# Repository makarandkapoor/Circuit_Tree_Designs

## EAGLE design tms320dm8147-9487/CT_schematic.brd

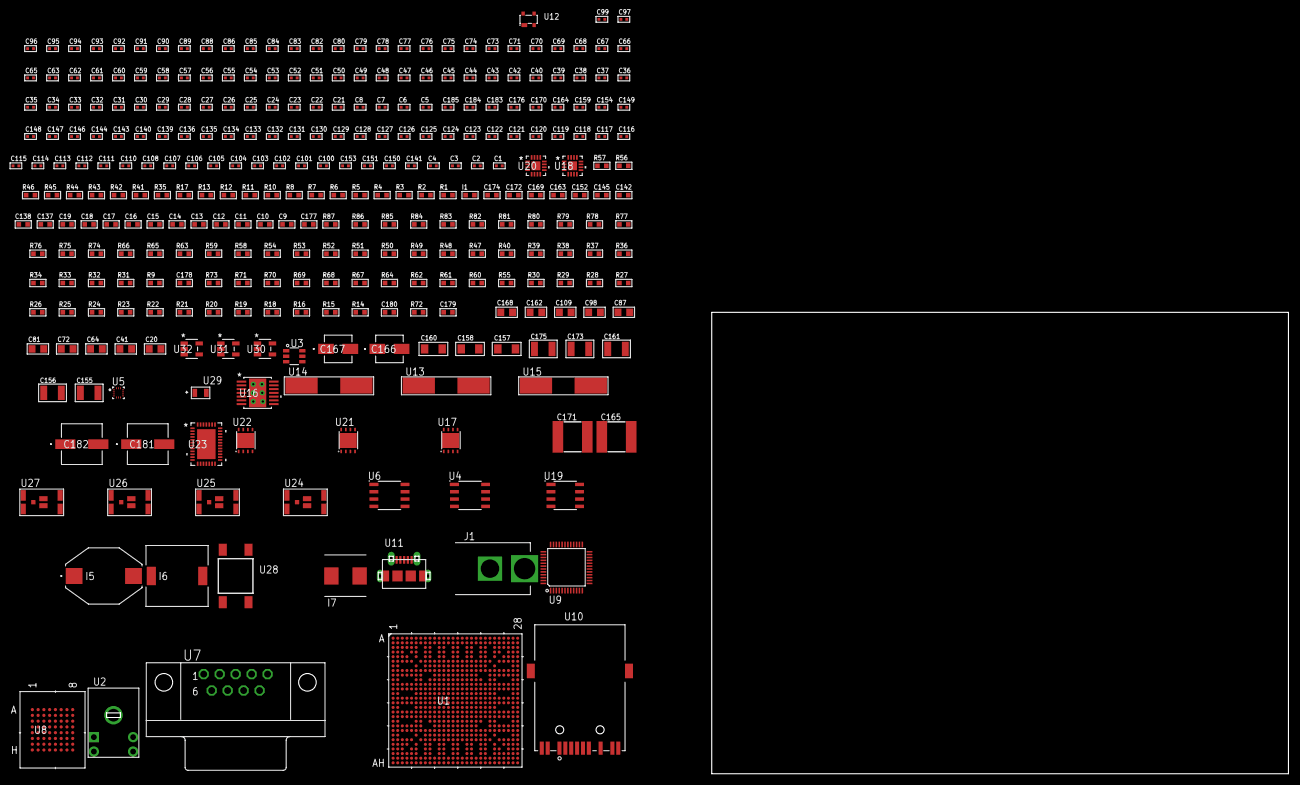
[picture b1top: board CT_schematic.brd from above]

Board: 2 copper layers, 309 parts (0 on the bottom side), 194 nets, no tracks yet.

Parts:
C1, C2, C3, C4: 1.2e-11; C0402
C5, C6, C7, C8, C21, C22, C23, C24, C25, C26, C27, C28, C29, C30, C42, C43, C44, C45, C46, C47, C48, C49, C50, C51, C52, C53, C54, C55, C56, C57, C58, C59, C60, C61, C62, C63, C65, C66, C67, C68, C69, C70, C71, C73, C74, C75, C76, C77, C78, C79, C80, C82, C83, C84, C85, C86, C135, C136, C143, C146, C148, C149, C154, C164, C170, C176: 1e-07; C0402
C9, C10, C11, C12, C13, C14, C15, C16, C17, C18, C19, C137, C138, C142, C145, C152, C163, C169, C172, C174: 1e-06; C0603
C20, C41, C64, C72, C81, C87, C98, C109, C162, C168: 1e-05; C0805
C31, C32, C33, C34, C35, C36, C37, C38, C39, C40, C88, C89, C90, C91, C92, C93, C94, C95, C96, C97, C99, C100, C101, C102, C103, C104, C105, C106, C107, C108, C110, C111, C112, C113, C114, C115, C116, C117, C118, C119, C120, C121, C122, C123, C124, C125, C126, C127, C128, C129, C130, C131, C132, C133, C134, C139, C140, C144, C147, C159, C183, C184, C185: 1e-08; C0402
C141: 2.2e-08; C0402
C150, C151: 2.7e-11; C0402
C153: 3.3e-09; C0402
C155, C156: 2.2e-05; C1210
C157, C158, C160: 1e-05; C1206
C161, C173, C175: 1e-05; C1210
C165, C171: 6.8e-05; 2220
C166: 1e-06; EXV-9B
C167: 2.2e-06; EXV-9B
C177: 2.2e-06; C0603
C178: 2.45e-08; R0603
C179: 2.8258362168397e-09; R0603
C180: 7.105e-09; R0603
C181, C182: 0.0001; EXV-9H
I1: 97.0; R0603
I5: 1.5e-06; IND_PM3316
I6: 2.5e-06; DR1040
I7: 3.3e-06; WE-HCI_7030/7040/7050
J1: PJ-037B; PJ-037B_PACKAGE
R1, R2, R3, R4, R46: 4700.0; R0603
R5, R6, R7, R8: 2200.0; R0603
R9, R63: 47000.0; R0603
R10, R11: 49.9; R0603
R12, R13: 2700.0; R0603
R14, R15, R16, R18, R19, R20, R21, R22, R23, R24, R25, R26, R27, R28, R29, R30, R55, R61, R62, R64, R68, R70, R71, R73: 100000.0; R0603
R17, R41, R42: 0.1; R0603
R31, R32, R33, R34, R36, R37, R38, R39, R40, R47, R48, R49, R50, R51, R52, R74, R76, R77, R82, R83, R84, R85, R86: 10000.0; R0603
R35: 120.0; R0603
R43, R44: 200.0; R0603
R45: 2490.0; R0603
R53: 15000.0; R0603
R54: 22000.0; R0603
R56: 3900.0; R0603
R57: 1000.0; R0603
R58, R65: 20000.0; R0603
R59: 27000.0; R0603
R60, R67, R69: 300000.0; R0603
R66: 91000.0; R0603
R72: 153694.38; R0603
R75, R87: 75000.0; R0603
R78, R79, R80, R81: 95300.0; R0603
U1: TMS320DM8147SCYE2; BFBGA-684
U2: MD-40S
U3: MAX4995AAUT+T; SOT-23-6
U4: AT25M01-SSHM-T; SOIC-8
U5: BMC150; LGA14R35P5X6_200X200X100
U6: MCP2562-E/SN; SOIC-8
U7: 182-009-113R531; 182-009-MALE
U8: MT28EW128ABA1HPC-0SIT; LBGA-64
U9: RTL8201FL-VB-CG
U10: 7498011122R
U11: 47590-0001; MICRO_USB_AB
U12: prtr5v0u2ax; SOT143B
U13, U14: ABLS-20.000MHZ-B4-T
U15: ABLS-25.000MHZ-B2F-T
U16: tps54525PWP; HTSSOP14
U17: LP3878SDX-ADJ/NOPB; WSON-8
U18, U20: LTC3601EUD#PBF; QFN-16_EP
U19: LP2954AIMX/NOPB; LP2954
U21, U22: LP2951ACSDX/NOPB; WSON-8
U23: LTC2928CUHF#PBF; QFN-38_UHF
U24, U25, U26, U27: IRF8306MTRPbF; IRF8306MTRPBF
U28: 4-1437565-2; SW_4-1437565-2
U29: Q65110A2395; LGM67K-G1J2-24-Z
U30, U31, U32: nc7sz125m5x; NC7SZ125M5X

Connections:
CLK_CRYSTAL_U1_AH2: C1.1, U1.AH2, U13.1
CLK_CRYSTAL_U1_AH3: C2.1, U1.AH3, U13.2
CLK_CRYSTAL_U1_R1: C3.1, U1.R1, U14.1
CLK_CRYSTAL_U1_T1: C4.1, U1.T1, U14.2
CLK_CRYSTAL_U9_42: C151.1, U9.42, U15.1
CLK_CRYSTAL_U9_43: C150.1, U9.43, U15.2
GND: C1.2, C2.2, C3.2, C4.2, C5.2, C6.2, C7.2, C8.2, C9.2, C10.2, C11.2, C12.2, C13.2, C14.2, C15.2, C16.2, C17.2, C18.2, C19.2, C20.2, C21.2, C22.2, C23.2, C24.2, C25.2, C26.2, C27.2, C28.2, C29.2, C30.2, C31.2, C32.2, C33.2, C34.2, C35.2, C36.2, C37.2, C38.2, C39.2, C40.2, C41.2, C42.2, C43.2, C44.2, C45.2, C46.2, C47.2, C48.2, C49.2, C50.2, C51.2, C52.2, C53.2, C54.2, C55.2, C56.2, C57.2, C58.2, C59.2, C60.2, C61.2, C62.2, C63.2, C64.2, C65.2, C66.2, C67.2, C68.2, C69.2, C70.2, C71.2, C72.2, C73.2, C74.2, C75.2, C76.2, C77.2, C78.2, C79.2, C80.2, C81.2, C82.2, C83.2, C84.2, C85.2, C86.2, C87.2, C88.2, C89.2, C90.2, C91.2, C92.2, C93.2, C94.2, C95.2, C96.2, C97.2, C98.2, C99.2, C100.2, C101.2, C102.2, C103.2, C104.2, C105.2, C106.2, C107.2, C108.2, C109.2, C110.2, C111.2, C112.2, C113.2, C114.2, C115.2, C116.2, C117.2, C118.2, C119.2, C120.2, C121.2, C122.2, C123.2, C124.2, C125.2, C126.2, C127.2, C128.2, C129.2, C130.2, C131.2, C132.2, C133.2, C134.2, C135.2, C136.2, C137.2, C138.2, C139.2, C140.2, C141.2, C142.2, C143.2, C144.2, C145.2, C146.2, C147.2, C148.2, C149.2, C150.2, C151.2, C152.2, C153.2, C155.2, C156.2, C157.2, C158.2, C159.2, C160.2, C161.2, C162.2, C163.2, C165.1, C165.2, C166.2, C167.2, C168.2, C169.2, C171.1, C171.2, C172.2, C173.2, C174.2, C175.2, C176.2, C177.2, C178.2, C179.2, C180.2, C181.2, C182.2, C183.2, C184.2, C185.2, J1.2, R9.2, R10.2, R11.2, R14.2, R15.2, R16.2, R17.2, R18.2, R19.2, R20.2, R21.2, R22.2, R23.2, R24.2, R25.2, R26.2, R27.2, R28.2, R29.2, R30.2, R41.2, R42.2, R45.2, R47.2, R49.2, R50.2, R54.2, R57.2, R58.2, R60.2, R64.2, R65.2, R67.2, R70.2, R73.2, R75.2, R78.2, R79.2, R80.2, R81.2, R82.2, R83.2, R84.2, R85.2, R86.2, U1.A1, U1.A12, U1.A17, U1.A28, U1.AA14, U1.AA16, U1.AA19, U1.AD21, U1.AE1, U1.AE2, U1.AE9, U1.AE20, U1.AF23, U1.AG1, U1.AG3, U1.AH1, U1.AH28, U1.D9, U1.D20, U1.E8, U1.E20, U1.J12, U1.J14, U1.J19, U1.K10, U1.K11, U1.K13, U1.K14, U1.K15, U1.K16, U1.K17, U1.K19, U1.L8, U1.L13, U1.L14, U1.L16, U1.L22, U1.M9, U1.M15, U1.M17, U1.M19, U1.M21, U1.N8, U1.N12, U1.N15, U1.N16, U1.N20, U1.N21, U1.N22, U1.P13, U1.P15, U1.P17, U1.P19, U1.P21, U1.R2, U1.R8, U1.R9, U1.R10, U1.R12, U1.R14, U1.R16, U1.R21, U1.R22, U1.T8, U1.T9, U1.T13, U1.T14, U1.T17, U1.T18, U1.T19, U1.T21, U1.T22, U1.U12, U1.U14, U1.U18, U1.U20, U1.U26, U1.V7, U1.V9, U1.V11, U1.V12, U1.V13, U1.V17, U1.V18, U1.V19, U1.V21, U1.W12, U1.W16, U1.W17, U1.Y1, U1.Y2, U1.Y10, U1.Y12, U1.Y15, U1.Y17, U1.Y18, U1.Y19, U1.Y26, U2.1, U2.2, U3.2, U4.4, U5.1, U5.6, U5.7, U5.9, U6.2, U6.8, U7.5, U8.E8, U8.H2, U8.H7, U9.7, U9.20, U9.33, U9.47, U10.11, U11.5, U11.6, U11.7, U11.8, U11.9, U12.1, U16.5, U16.8, U16.9, U16.15, U17.3, U17.PAD, U18.1, U18.9, U18.17, U19.4, U20.1, U20.9, U20.17, U21.3, U21.4, U21.PAD, U22.3, U22.4, U22.PAD, U23.10, U23.12, U23.13, U23.24, U23.25, U23.39, U30.1, U30.3, U31.1, U31.3, U32.1, U32.3
NET_U1_AA15: U1.AA15, U1.AA17, U1.AB14, U1.AB16, U1.M8, U1.N7, U1.P8, U1.T7, U1.U21, U1.U22, U1.V20, U1.Y11, U1.Y16
NET_U1_AB6: R6.1, U1.AB6, U5.14
NET_U1_AC4: R5.1, U1.AC4, U5.11
NET_U1_AG22: R13.2, U1.AG22
NET_U1_AG23: R12.2, U1.AG23
NET_U1_B1: R11.1, U1.B1
NET_U1_B27: R10.1, U1.B27
NET_U1_G14: C7.1, C8.1, U1.G14
NET_U1_G15: C5.1, C6.1, U1.G15
NET_U1_H28: R7.1, U1.H28, U9.30
NET_U1_J5: R3.1, U1.J5, U32.4
NET_U1_K12: U1.K9, U1.K12, U1.K18, U1.L15, U1.L17, U1.L19, U1.M16, U1.M18, U1.N17, U1.N19, U1.P12, U1.P14, U1.P16, U1.R15, U1.R17, U1.R19, U1.T12, U1.U11, U1.U13, U1.U17, U1.U19, U1.W11
NET_U1_L18: C13.1, U1.L18
NET_U1_M11: C15.1, U1.M11
NET_U1_N10: C16.1, U1.N10
NET_U1_N11: C17.1, U1.N11
NET_U1_P10: C14.1, U1.P10
NET_U1_P18: C11.1, U1.P18
NET_U1_P24: R8.1, U1.P24, U9.31
NET_U1_R11: C12.1, U1.R11
NET_U1_T10: C18.1, U1.T10
NET_U1_T11: C19.1, U1.T11
NET_U1_U10: U1.U9, U1.U10
NET_U1_V14: C10.1, U1.V14
NET_U1_W10: U1.W9, U1.W10
NET_U1_W14: C9.1, U1.W14
NET_U1_W19: U1.W19, U1.W20
NET_U2_3: U1.AH24, U2.3
NET_U2_4: U1.AH22, U2.4
NET_U3_3: R9.1, U3.3
NET_U3_4: U1.AF11, U3.4
NET_U4_3: R31.1, U4.3
NET_U4_7: R33.1, U4.7
NET_U6_6: R35.2, U6.6
NET_U7_2: R35.2, U6.6, U7.2
NET_U7_3: R35.1, U6.7, U7.3
NET_U8_B4: R39.1, U8.B4
NET_U8_B5: R2.1, U8.B5, U31.4
NET_U9_6: C142.1, C143.1, C144.1, I1.1, U9.6, U9.41
NET_U9_10: R50.1, U9.10
NET_U9_29: R1.1, U9.29, U30.4
NET_U9_32: R46.1, U9.32
NET_U9_34: R48.1, U9.34
NET_U9_35: R49.1, U9.35
NET_U9_40: C149.1, U9.40
NET_U9_46: R45.1, U9.46
NET_U9_48: C148.1, U9.48
NET_U10_1: U9.1, U10.1
NET_U10_3: U9.2, U10.3
NET_U10_4: U9.4, U10.4
NET_U10_5: C141.1, U10.2, U10.5
NET_U10_6: U9.5, U10.6
NET_U10_8: R42.1, U10.8
NET_U10_10: R43.1, U10.10
NET_U10_12: R44.1, U10.12
NET_U10_13: R41.1, U10.13, U10.14
NET_U16_2: R53.2, R54.1, U16.2
NET_U16_3: C152.1, U16.3
NET_U16_4: C153.1, U16.4
NET_U16_10: C154.1, I5.1, U16.10, U16.11
NET_U16_12: C154.2, U16.12
NET_U17_1: C159.1, U17.1
NET_U17_6: R56.2, R57.1, U17.6
NET_U17_8: R55.1, U17.8
NET_U18_3: C164.2, I6.1, U18.3, U18.4
NET_U18_6: C164.1, U18.6
NET_U18_7: C163.1, U18.7, U18.12
NET_U18_10: R60.1, U18.10
NET_U18_11: R58.1, R59.1, U18.11
NET_U18_ATNET_3: I6.2, R59.2
NET_U19_3: R62.1, U19.3
NET_U19_5: R61.1, U19.5
NET_U19_7: R63.2, R64.1, U19.7
NET_U20_3: C170.2, I7.1, U20.3, U20.4
NET_U20_6: C170.1, U20.6
NET_U20_7: C169.1, U20.7, U20.12
NET_U20_10: R67.1, U20.10
NET_U20_11: R65.1, R66.1, U20.11
NET_U20_ATNET_3: I7.2, R66.2
NET_U21_5: R68.1, U21.5
NET_U21_7: R69.2, R70.1, U21.7
NET_U22_5: R71.1, U22.5
NET_U22_7: R72.2, R73.1, U22.7
NET_U23_3: R83.1, U23.3
NET_U23_6: R78.1, U23.6
NET_U23_7: R79.1, U23.7
NET_U23_8: R80.1, U23.8
NET_U23_9: R81.1, U23.9
NET_U23_16: R82.1, R87.1, U23.16
NET_U23_18: R77.1, U23.18
NET_U23_19: R76.1, U23.19, U23.20
NET_U23_21: R74.1, R75.1, U23.21, U30.2, U31.2, U32.2
NET_U23_22: C176.1, R74.2, R76.2, R77.2, U23.11, U23.22
NET_U23_26: C179.1, U23.26
NET_U23_27: C178.1, U23.27
NET_U23_28: C180.1, U23.28
NET_U23_30: R86.1, U23.30
NET_U23_32: R85.1, U23.32
NET_U23_38: R84.1, U23.38
NET_U24_3: U23.2, U24.3
NET_U25_3: U23.37, U25.3
NET_U26_3: U23.31, U26.3
NET_U27_3: U23.29, U27.3
NET_U28_1: U28.1, U28.2
NET_U28_3: U28.3, U28.4
PROC_DCAN0_RX: U1.AG6, U6.4
PROC_DCAN0_TX: U1.AH6, U6.1
PROC_EMAC0_MRCLK: U1.H27, U9.19
PROC_EMAC0_MRXD0: U1.G28, U9.14
PROC_EMAC0_MRXD1: U1.P23, U9.16
PROC_EMAC0_MRXD2: U1.R23, U9.17
PROC_EMAC0_MRXD3: R51.1, U1.J25, U9.18
PROC_EMAC0_MRXDV: R47.1, U1.K22, U9.13
PROC_EMAC0_MRXER: R52.1, U1.J26, U9.39
PROC_EMAC1_MCOL: U1.AC24, U9.38
PROC_EMAC1_MCRS: U1.AA23, U9.36
PROC_EMAC1_MTCLK: U1.AE24, U9.22
PROC_EMAC1_MTXD0: U1.AF26, U9.23
PROC_EMAC1_MTXD1: U1.AE26, U9.24
PROC_EMAC1_MTXD2: U1.AD26, U9.25
PROC_EMAC1_MTXD3: U1.AG27, U9.26
PROC_EMAC1_MTXEN: U1.Y24, U9.27
PROC_GPIO_TO_U1_USB_FAULT: U1.AC16, U3.6
PROC_GPMC_A1: U1.T23, U8.E2
PROC_GPMC_A2: U1.H26, U8.D2
PROC_GPMC_A3: U1.M24, U8.C2
PROC_GPMC_A4: U1.L26, U8.A2
PROC_GPMC_A5: U1.AD18, U8.B2
PROC_GPMC_A6: U1.AC18, U8.D3
PROC_GPMC_A7: U1.AC19, U8.C3
PROC_GPMC_A8: U1.AA22, U8.A3
PROC_GPMC_A9: U1.AE23, U8.B6
PROC_GPMC_A10: U1.AD23, U8.A6
PROC_GPMC_A11: U1.AB23, U8.C6
PROC_GPMC_A12: U1.AF18, U8.D6
PROC_GPMC_A13: U1.J22, U8.B7
PROC_GPMC_A14: U1.H24, U8.A7
PROC_GPMC_A15: U1.J23, U8.C7
PROC_GPMC_A16: U1.AD27, U8.D7
PROC_GPMC_A17: U1.V23, U8.E7
PROC_GPMC_A18: U1.AE28, U8.B3
PROC_GPMC_A19: U1.AC27, U8.C4
PROC_GPMC_A20: U1.AD28, U8.D5
PROC_GPMC_A21: U1.AC28, U8.D4
PROC_GPMC_A22: R17.1, U1.AB27, U8.C5
PROC_GPMC_A23: U1.R24, U8.B8
PROC_GPMC_BE0_CLE: R40.1, U1.U27, U8.F7
PROC_GPMC_CS0: R36.1, U1.T28, U8.F2
PROC_GPMC_D0: R18.1, U1.U26, U8.E3
PROC_GPMC_D1: R19.1, U1.Y28, U8.H3
PROC_GPMC_D2: R20.1, U1.V27, U8.E4
PROC_GPMC_D3: R21.1, U1.W27, U8.H4
PROC_GPMC_D4: R22.1, U1.V26, U8.H5
PROC_GPMC_D5: R16.1, U1.AA28, U8.E5
PROC_GPMC_D6: R15.1, U1.U25, U8.H6
PROC_GPMC_D7: R14.1, U1.V25, U8.E6
PROC_GPMC_D8: R26.1, U1.Y27, U8.F3
PROC_GPMC_D9: R25.1, U1.AB28, U8.G3
PROC_GPMC_D10: R27.1, U1.Y26, U8.F4
PROC_GPMC_D11: R23.1, U1.AA27, U8.G4
PROC_GPMC_D12: R28.1, U1.U24, U8.F5
PROC_GPMC_D13: R30.1, U1.U23, U8.G6
PROC_GPMC_D14: R29.1, U1.V24, U8.F6
PROC_GPMC_D15: R24.1, U1.Y25, U8.G7
PROC_GPMC_OE_RE_B: R37.1, U1.T27, U8.G2
PROC_GPMC_WAIT0: U1.W28, U8.A4
PROC_GPMC_WE_B: R38.1, U1.U28, U8.A5
PROC_SPI0_D0: U1.AE3, U4.5
PROC_SPI0_D1: U1.AF3, U4.2
PROC_SPI0_SCLK: U1.AC7, U4.6
PROC_SPI0_SCS0: R32.1, U1.AD6, U4.1
PROC_USB0_DM: U1.AH11, U11.2, U12.3
PROC_USB0_DP: U1.AG11, U11.3, U12.2
PROC_USB0_ID: U1.AG10, U11.4
PROC_USB0_VBUSIN: U1.AG12, U3.1, U11.1, U12.4
VCC_9V5: C177.1, C181.1, C182.1, J1.1, R87.2, U23.23, U24.1, U24.2, U24.6, U24.7, U25.1, U25.2, U25.6, U25.7, U26.1, U26.2, U26.6, U26.7, U27.1, U27.2, U27.6, U27.7
VCC_S1_9V5: C157.1, C158.1, C160.1, R55.2, U16.7, U16.13, U16.14, U17.4, U24.4, U24.5
VCC_S2_9V5: C162.1, U18.15, U18.16, U25.4, U25.5
VCC_S3_9V5: C166.1, C168.1, C172.1, R62.2, U19.8, U20.15, U20.16, U21.8, U26.4, U26.5
VCC_S4_9V5: C174.1, U22.8, U27.4, U27.5
VCC_TIER1_1V28: C41.1, C42.1, C43.1, C44.1, C45.1, C46.1, C47.1, C48.1, C49.1, C50.1, C51.1, C52.1, C53.1, C54.1, C55.1, C56.1, C57.1, C58.1, C59.1, C60.1, C61.1, C62.1, C63.1, C64.1, C65.1, C66.1, C67.1, C68.1, C69.1, C70.1, C71.1, C72.1, C73.1, C74.1, C75.1, C76.1, C77.1, C78.1, C79.1, C80.1, C81.1, C82.1, C83.1, C84.1, C85.1, C86.1, C155.1, C156.1, I5.2, R53.1, U1.K9, U1.K10, U1.L9, U1.L10, U1.L11, U1.L12, U1.L14, U1.L15, U1.M10, U1.M12, U1.M13, U1.M14, U1.N9, U1.N13, U1.N14, U1.T14, U1.T15, U1.T16, U1.U15, U1.U16, U1.V15, U1.V16, U16.1
VCC_TIER1_5V0: C161.1, R56.1, U3.5, U17.5
VCC_TIER2_1V43: C87.1, C88.1, C89.1, C90.1, C91.1, C92.1, C93.1, C94.1, C95.1, C96.1, C97.1, C98.1, C99.1, C100.1, C101.1, C102.1, C103.1, C104.1, C105.1, C106.1, C107.1, C108.1, C165.2, I6.2, R59.2, U1.E8, U1.E9, U1.E20, U1.E21, U1.G13, U1.G16, U1.H12, U1.H13, U1.H14, U1.H16, U1.H17, U1.J10, U1.J11, U1.J13, U1.J15, U1.J16, U1.J17, U1.J18, U18.8
VCC_TIER3_1V8: C36.1, C37.1, C38.1, C39.1, C109.1, C110.1, C111.1, C112.1, C113.1, C114.1, C115.1, C116.1, C117.1, C118.1, C119.1, C120.1, C121.1, C122.1, C123.1, C124.1, C125.1, C126.1, C127.1, C128.1, C129.1, C130.1, C131.1, C132.1, C133.1, C135.1, C167.1, C183.1, C184.1, C185.1, R61.2, R63.1, U1.AA12, U1.AA18, U1.AB18, U1.AB19, U1.H15, U1.L20, U1.M7, U1.M22, U1.N18, U1.P7, U1.P9, U1.P11, U1.P20, U1.R10, U1.R13, U1.R18, U1.R20, U1.T20, U1.U7, U1.U9, U1.V10, U1.W9, U1.W13, U1.W15, U1.W18, U1.Y13, U5.8, U19.1, U30.5, U31.5, U32.5
VCC_TIER3_3V3: C20.1, C21.1, C22.1, C23.1, C24.1, C25.1, C26.1, C27.1, C28.1, C29.1, C30.1, C31.1, C32.1, C33.1, C34.1, C35.1, C134.1, C136.1, C138.1, C139.1, C140.1, C145.1, C146.1, C147.1, C171.2, I1.2, I7.2, R1.2, R2.2, R3.2, R4.2, R5.2, R6.2, R7.2, R8.2, R31.2, R32.2, R33.2, R34.1, R34.2, R36.2, R37.2, R38.2, R39.2, R40.2, R46.2, R48.2, R51.2, R52.2, R66.2, U1.K20, U1.L21, U1.M8, U1.M20, U1.N7, U4.8, U5.10, U5.12, U5.13, U6.5, U8.D8, U8.F1, U8.G5, U9.15, U9.21, U9.37, U20.8
VCC_TIER3_5V0: C137.1, C173.1, R68.2, R69.1, U6.3, U21.1
VCC_TIER4_3V3: C40.1, C175.1, R71.2, R72.1, U1.AA13, U22.1
